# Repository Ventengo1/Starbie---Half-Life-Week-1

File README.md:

# Starbie---Half-Life-Week-1

So made this as my first ever PCB that will actually work (fingers crossed) as part of week 1 of Hack Club Half Life.

***So what is Starbie?***

Starbie is a tiny motion controlled digital pet, in the shape of a star, with 2 tiny gameplay buttons. Instead of pressing much, you interact with board physcially. 
It is meant to sit on your desk, show you persoanlity, be with you on the go, or whatever you want for it to be.

***What is it made of***

Starbie is made of a microcontorller, oled display, motion sensor, environment senor, and 2 buttons. It is USB powered and is beginner friendly (for me :).. )

The Bill of Materials here is from the offical Starbie github repo (https://github.com/SharKingStudios/Starbie):

Here is a pic of the board: 

FOR BOM on Half Life Dashboard, not sure of prices as Hack Club can mass order so hopefully you guys get better prices than me and can ship for cheap. Just used BOM from the official starbie github repo

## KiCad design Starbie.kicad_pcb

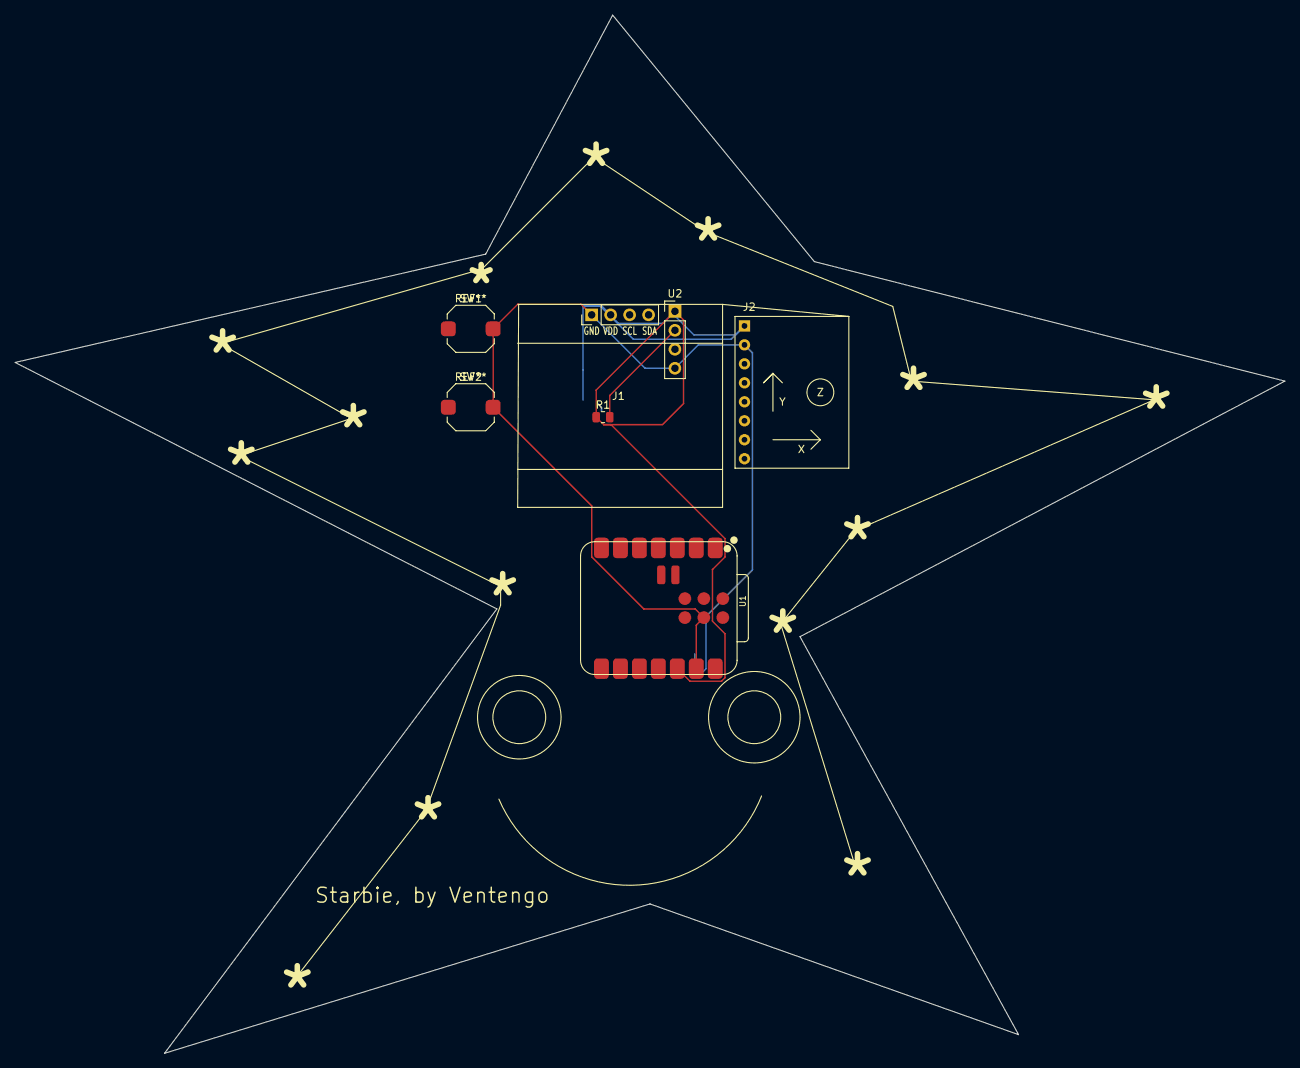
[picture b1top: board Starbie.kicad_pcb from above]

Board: 2 copper layers, 170.0 x 139.0 mm, 7 parts (0 on the bottom side), 3 nets.

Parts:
J1: Conn_01x04_Pin; Display_128x64_096_I2C
J2: Conn_01x08_Pin; MPU6050_Module
R1: 10k; R_0805_2012Metric
SW1, SW2: SW_Push; SW_Push_1TS009xxxx-xxxx-xxxx_6x6x5mm
U1: XIAO-ESP32-C3-SMD
U2: DHT11; PinHeader_1x04_P2.54mm_Vertical

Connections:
+3.3V: J1.2, J2.1, R1.1, U1.12 (3V3_OUT), U2.1 (VDD)
GND: J1.1, J2.2, SW1.2 (2_2), SW2.2 (2_2), U1.13 (GND), U1.18 (GND), U2.4 (GND)
unnamed: R1.2, U2.2 (DATA)
